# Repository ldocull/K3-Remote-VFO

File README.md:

# K3-Remote-VFO
Remote VFO and Button Interface for Elecraft, Kenwood and other radio transceivers

## Introduction
The system is comprised of two pieces
 - A Remote Controls Unit
 - A Connector Interface to the Rig 

The Connector Interface goes between the control PC and the Rig using classic RS-232. This system is not currently set up to support modern USB interfaces. The main Remote control is tethered to the Connector Interface using a RJ12 (6P/6J) straight-through cable.  Power (5VDC) is supplied to the device from a USB port or power supply to the Connector Interface via a micro-USB jack.

## About the Design Data

The Mechanics were designed in Fusion 360, A full step-assembly is in the repo which could be pulled into any modern CAD package for alteration.   

The construction is plastic. The case frame was FDM printed from PLA, and the top/bottom were laser cut from 
0.08" acrylic. The main-dial and keycaps were SLA (resin) printed on an [Elegoo Mars](https://www.elegoo.com/collections/3d-printing/products/elegoo-mars-3-lcd-3d-printer) printer.

The Electronics were designed in KiCAD. KiCAD is free and easy to use, so this should be a good start for further work. I used [JLCPCB](https://jlcpcb.com/) to manufacture the PCBs.

The Software is Arduino-based and runs on a [STM32F103C8 BlackPill](https://hobbycomponents.com/st-micro-electronics/960-stm32f103-black-pill-development-board). The project is in Visual Studio Code, and PlatformIO which are currently both free tools.  The Maple bootloader was installed to make the development quick and easy and is included in the repo.

## Updating Encoder and Key Definitions

The keys are assigned text-macros which are stored in non-volatile memory on the Remote unit. The encoder-wheel is handled the same way. The wheel can be pressed and therefore the operation has been divided into four "speeds" (as is indicated by the LEDs below the wheel.)  In the case of the encoder, the macros are also divided into four sets up ***"up"*** and ***"down"*** movements and the text contents are transmitted on each pulse of the wheel.

The default baud rate is ***38400*** and the Remote can be updated in-situ using a terminal emulator such as [RealTerm](https://realterm.sourceforge.io/).   

The following text could be uploaded to the remote.  `'$$$'` is used to mark the beginning of the upload, and `'&&&'` is used to end the upload.  Note that the macros are defined as ```<Kx> text message </K>'``` and `<Ex> text message </E>`. 

> (*Note the messages defined below are for the Elecraft K3.)*

```
$$$			// 3 dollar start of file

<K0>SWT11;</K>  //  A/B  menus stuff here...
<K1>SWT13;</K>  // A->B
<K2>SWT42;</K>  // SPOT

<K3>SWT29;</K>  // XFILT

<K4>SWT21;</K>  // M1-M2
<K5>SWT31;</K>  
<K6>SWT35;</K>  
<K7>SWT39;</K>  

<E0>UP4;</E>    // encoder modes here 0-3, increment/decrement
<E1>DN4;</E>    

<E2>UP8;</E>    
<E3>DN8;</E>    

<E4>UP1;</E>    
<E5>DN1;</E>    

<E6>UP0;</E>    
<E7>DN0;</E>	// end of file is ampersand

&&&
```

### Enjoy, 73,  de WR9R

___
Let us know that this work has been helpful to you.  Any proceeds will be used to offset expenses and further the art.

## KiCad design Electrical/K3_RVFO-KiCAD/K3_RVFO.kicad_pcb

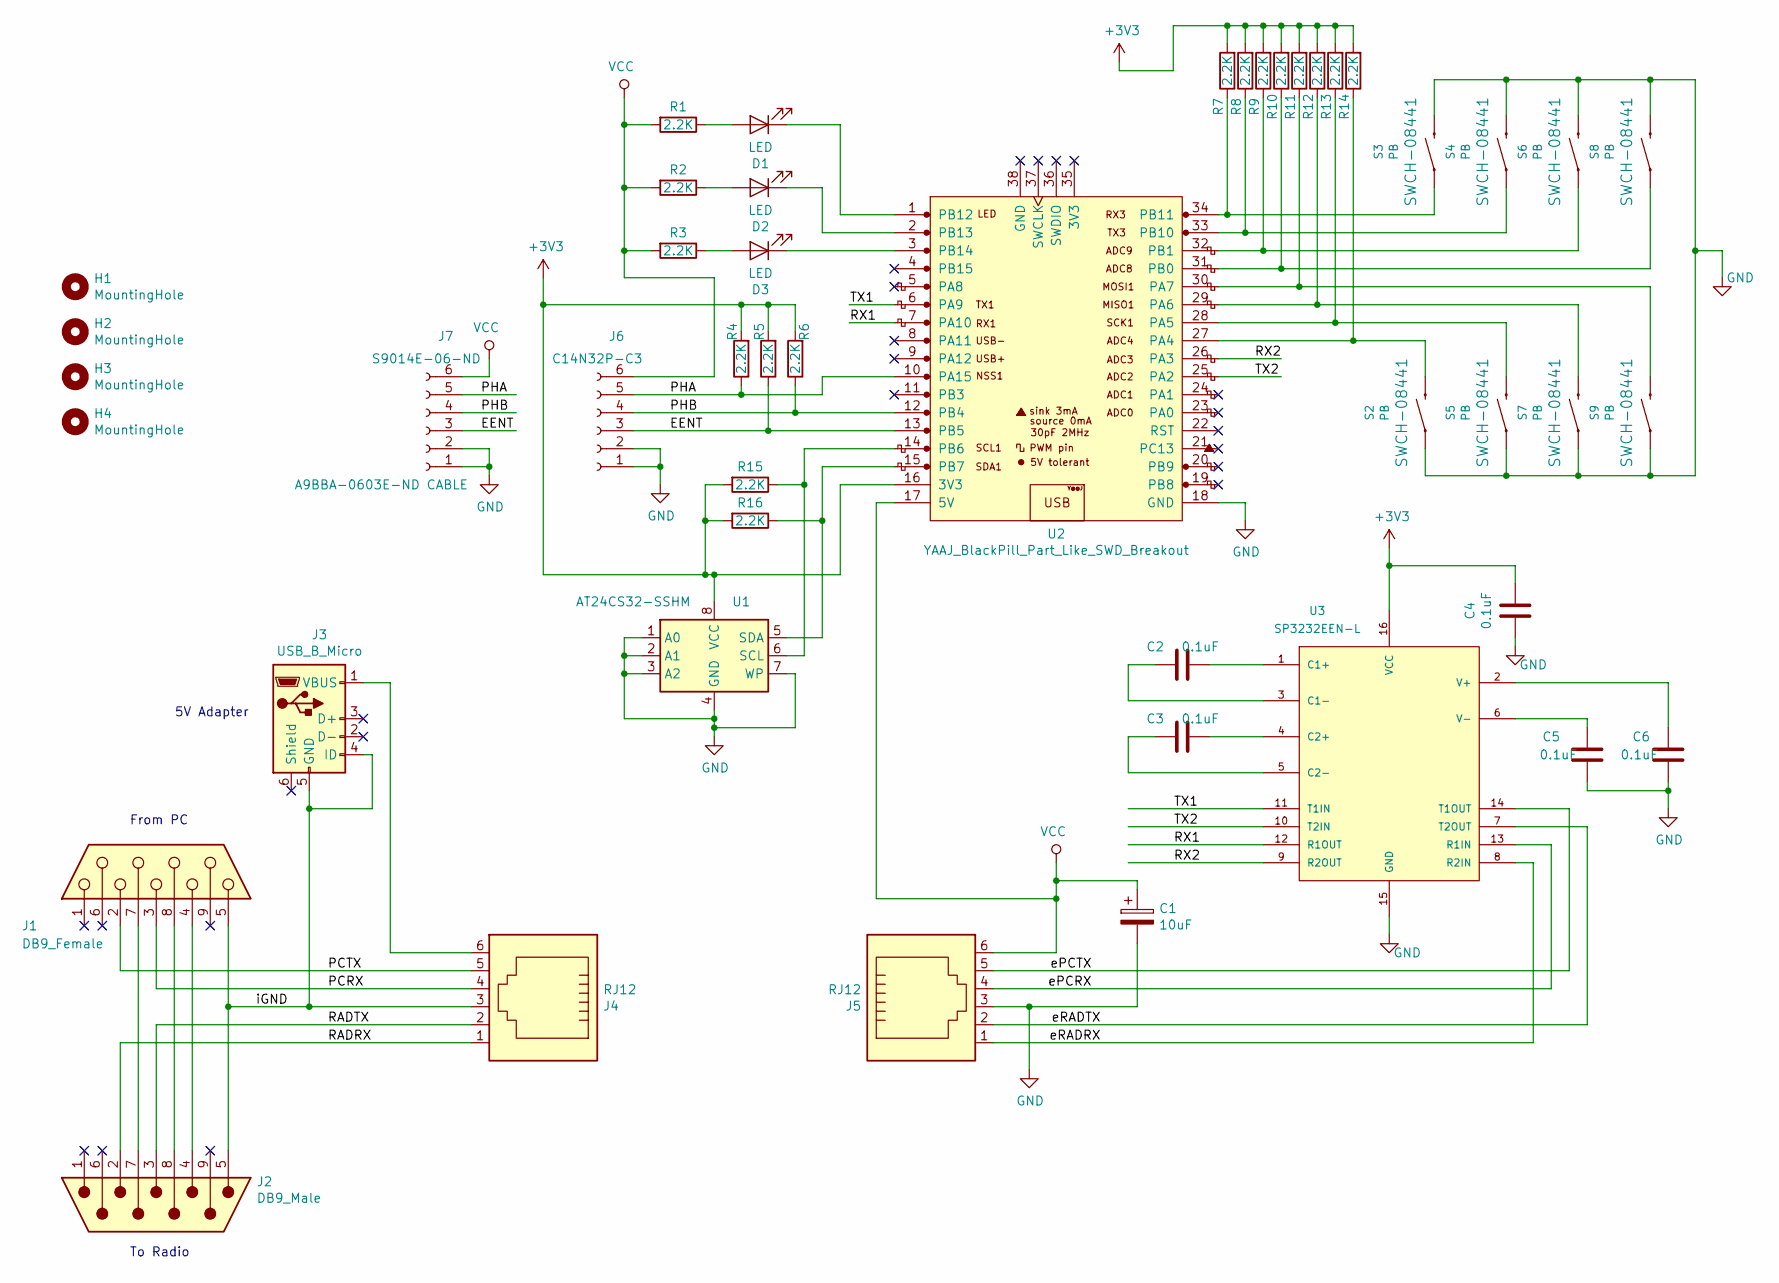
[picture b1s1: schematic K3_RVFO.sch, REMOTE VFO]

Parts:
C1: 10uF; CP_Elec_4x5.7; JLCPCB C59932
C2, C3, C4, C5, C6: 0.1uF; 0805; JLCPCB C2594299
D1, D2, D3: LED; LED_3MM
H1, H2, H3, H4: MountingHole; MountingHole_3mm_Pad
J1: DB9_Female; DSUB-9_Female_Horizontal_P2.77x2.84mm_EdgePinOffset4.94mm_H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
J2: DB9_Male; DSUB-9_Male_Horizontal_P2.77x2.84mm_EdgePinOffset4.94mm_Hou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
J3: USB_B_Micro; USB_Micro-B_Molex-105017-0001; JLCPCB C10418
J4, J5: RJ12; RJ12_Amphenol_54601
J6: C14N32P-C3; PinHeader_1x06_P2.54mm_Vertical
J7: S9014E-06-ND; PinHeader_1x06_P1.27mm_Vertical
R1, R2, R3, R4, R5, R6, R7, R8, R9, R10, R11, R12, R13, R14, R15, R16: 2.2K; R_0805_2012Metric; JLCPCB C17520
S2, S3, S4, S5, S6, S7, S8, S9: PB; TACTILE_SWITCH_PTH_6.0MM
U1: AT24CS32-SSHM; SOIC-8_3.9x4.9mm_P1.27mm
U2: YAAJ_BlackPill_Part_Like_SWD_Breakout; YAAJ_BlackPill_SWD_2
U3: SP3232EEN-L; SO16; JLCPCB C9378

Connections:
+3V3: C4.1, R4.2, R5.2, R6.2, R7.2, R8.2, R9.2, R10.2, R11.2, R12.2, R13.2, R14.2, R15.2, R16.2, U1.8 (VCC), U2.16 (3V3), U3.16 (VCC)
/EENT: J6.3, J7.3, R5.1, U2.13 (PB5)
/PCRX: J1.3, J4.4
/PCTX: J1.2, J4.5
/PHA: J6.5, J7.5, R4.1, U2.10 (PA15)
/PHB: J6.4, J7.4, R6.1, U2.12 (PB4)
/RADRX: J2.2, J4.1
/RADTX: J2.3, J4.2
/RX1: U2.7 (PA10), U3.12 (R1OUT)
/RX2: U2.26 (PA3), U3.9 (R2OUT)
/TX1: U2.6 (PA9), U3.11 (T1IN)
/TX2: U2.25 (PA2), U3.10 (T2IN)
/ePCRX: J5.4, U3.13 (R1IN)
/ePCTX: J5.5, U3.14 (T1OUT)
/eRADRX: J5.1, U3.8 (R2IN)
/eRADTX: J5.2, U3.7 (T2OUT)
/iGND: J1.5, J2.5, J3.4 (ID), J3.5 (GND), J4.3
GND: C1.2, C4.2, C5.2, C6.2, J5.3, J6.1, J6.2, J7.1, J7.2, S2.1, S3.3 (2), S4.3 (2), S5.1, S6.3 (2), S7.1, S8.3 (2), S9.1, U1.1 (A0), U1.2 (A1), U1.3 (A2), U1.4 (GND), U1.7 (WP), U2.18 (GND), U3.15 (GND)
unnamed: C2.1, U3.1 (C1+)
unnamed: C2.2, U3.3 (C1-)
unnamed: C3.1, U3.4 (C2+)
unnamed: C3.2, U3.5 (C2-)
unnamed: C5.1, U3.6 (V-)
unnamed: C6.1, U3.2 (V+)
unnamed: D1.1 (K), U2.1 (PB12)
unnamed: D1.2 (A), R1.1
unnamed: D2.1 (K), U2.2 (PB13)
unnamed: D2.2 (A), R2.1
unnamed: D3.1 (K), U2.3 (PB14)
unnamed: D3.2 (A), R3.1
unnamed: J1.4, J2.4
unnamed: J1.7, J2.7
unnamed: J1.8, J2.8
unnamed: J3.1 (VBUS), J4.6
unnamed: R7.1, S3.1, U2.34 (PB11)
unnamed: R8.1, S4.1, U2.33 (PB10)
unnamed: R9.1, S6.1, U2.32 (PB1)
unnamed: R10.1, S8.1, U2.31 (PB0)
unnamed: R11.1, S9.3 (2), U2.30 (PA7)
unnamed: R12.1, S7.3 (2), U2.29 (PA6)
unnamed: R13.1, S5.3 (2), U2.28 (PA5)
unnamed: R14.1, S2.3 (2), U2.27 (PA4)
unnamed: R15.1, U1.6 (SCL), U2.14 (PB6)
unnamed: R16.1, U1.5 (SDA), U2.15 (PB7)
VCC: C1.1, J5.6, J6.6, J7.6, R1.2, R2.2, R3.2, U2.17 (5V)

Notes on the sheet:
5V Adapter
From PC
To Radio

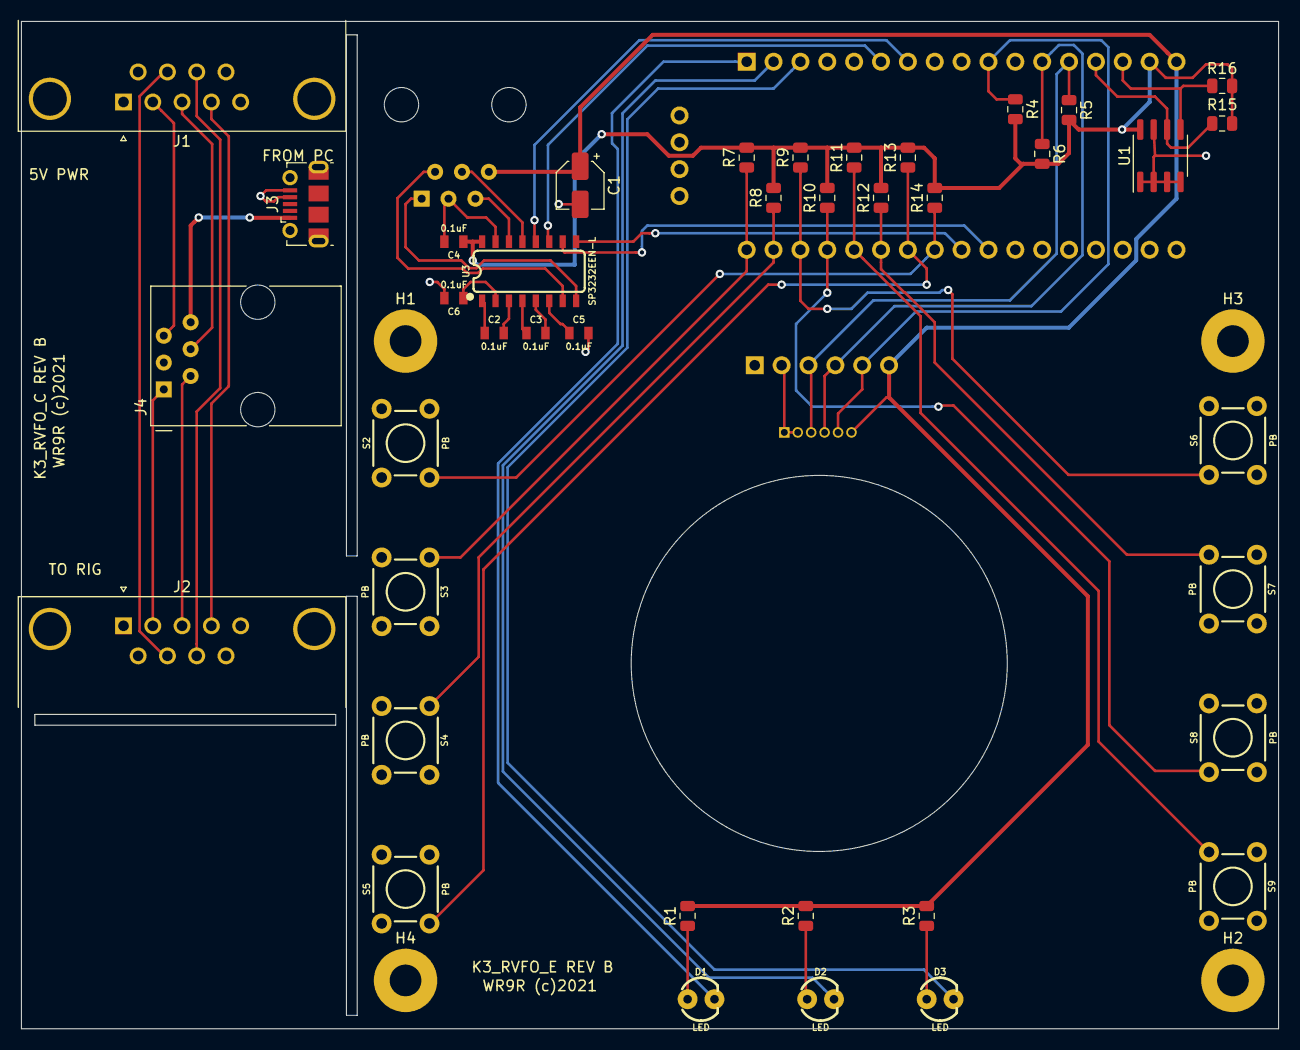
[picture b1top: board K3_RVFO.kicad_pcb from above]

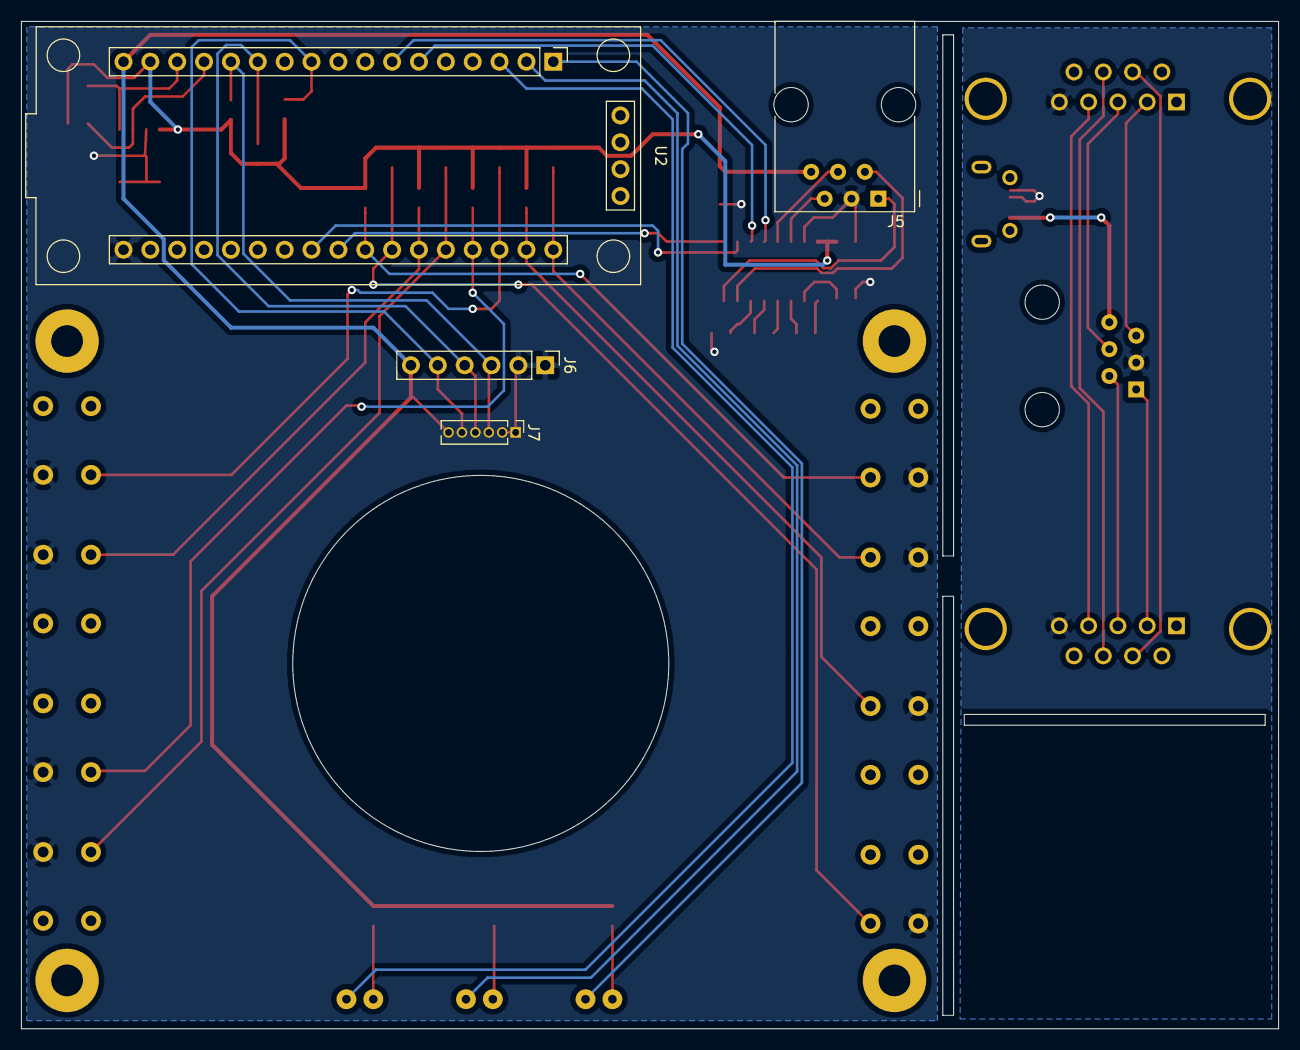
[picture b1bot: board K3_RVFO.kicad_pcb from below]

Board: 2 copper layers, 118.9 x 95.3 mm, 47 parts (4 on the bottom side), 45 nets.

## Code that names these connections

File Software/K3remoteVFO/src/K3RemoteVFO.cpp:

/*
  K3 REMOTE VFO

  2021/12/22
  (c)WR9R  Larry O'Cull 2021  LDO Systems LLC
 */

#include <Arduino.h>
#include "wheel.h"
#include "EE24C32.h"

EE24C32 EEPROM(0x50);
USBSerial COMM_PORT;

#define PC_LINK Serial1
#define RIG_LINK Serial2
#define HOST_SIDE PC_LINK
//#define HOST_SIDE COMM_PORT  // -- for using USB port for configuration

#define KEY0  PA4
#define KEY1  PB11
#define KEY2  PB10
#define KEY3  PA5
#define KEY4  PB1
#define KEY5  PA6
#define KEY6  PB0
#define KEY7  PA7
#define ENTER PB5

#define LED0  PB12
#define LED1  PB13
#define LED2  PB14

#define MAX_WHEEL_MODE 3
#define MAX_MESSAGE_INDEX 8
#define MAX_ENCMES_INDEX 8
#define MAX_MESSAGE_SIZE 128

struct EPROM_PLAN 
{
    uint8_t checkValue = 0x14;
    
    char keyMessage[MAX_MESSAGE_INDEX][MAX_MESSAGE_SIZE] = {
        {"SWT09;"},   // BAND +
        {"SWT10;"},   // BAMD -
        {"SWT17;"},   // MODE ++
        {"SWT29;"},   // XFIL
        {"SWT21;"},   // M1-M4...
        {"SWT31;"},
        {"SWT35;"},
        {"SWT39;"}};
    
    char encMessage[MAX_MESSAGE_INDEX][MAX_MESSAGE_SIZE] = {
        {"UP0;"},    // encoder base
        {"DN0;"},
        {"UP1;"},    // encoder up 1 level
        {"DN1;"},
        {"UP8;"},    // encoder up 2nd level
        {"DN8;"},
        {"UP4;"},    // encoder up 3nd level
        {"DN4;"}};

    int wheelMode = 0;

} rigSettings, backupSettings;

int initialized = 0;

// the setup function runs once when you press reset or power the board
void setup() {
  // initialize digital pin PB1 as an output.
  pinMode(LED0, OUTPUT);
  pinMode(LED1, OUTPUT);
  pinMode(LED2, OUTPUT);

  pinMode(KEY0,INPUT_PULLUP);
  pinMode(KEY1,INPUT_PULLUP);
  pinMode(KEY2,INPUT_PULLUP);
  pinMode(KEY3,INPUT_PULLUP);
  pinMode(KEY4,INPUT_PULLUP);
  pinMode(KEY5,INPUT_PULLUP);
  pinMode(KEY6,INPUT_PULLUP);
  pinMode(KEY7,INPUT_PULLUP);
  pinMode(ENTER,INPUT_PULLUP);

  PC_LINK.begin(38400); // PC side of life..  

  pinMode(PA3,INPUT_PULLUP);
  pinMode(PA2,OUTPUT);
  RIG_LINK.begin(38400); // Rig side of life..
  init_Encoder();
   COMM_PORT.begin(115200);
}

// lists the values of the stored message/macros for keys and encoder
void printMacros()
{
    int i;
      
    for(i=0; i< MAX_MESSAGE_INDEX; i++)
    {
      HOST_SIDE.print("<K");
      HOST_SIDE.print(i);
      HOST_SIDE.print(">");
      HOST_SIDE.print(rigSettings.keyMessage[i]);
      HOST_SIDE.println("</K>");
    }

    for(i=0; i< MAX_ENCMES_INDEX; i++)
    {
      HOST_SIDE.print("<E");
      HOST_SIDE.print(i);
      HOST_SIDE.print(">");
      HOST_SIDE.print(rigSettings.encMessage[i]);
      HOST_SIDE.println("</E>");
    }
}

// returns a key value 1-8 (9 for main dial), 0 if none pressed
int getKeyPress()
{
  if(!digitalRead(KEY0)) return 1;
  if(!digitalRead(KEY1)) return 2;
  if(!digitalRead(KEY2)) return 3;
  if(!digitalRead(KEY3)) return 4;
  if(!digitalRead(KEY4)) return 5;
  if(!digitalRead(KEY5)) return 6;
  if(!digitalRead(KEY6)) return 7;
  if(!digitalRead(KEY7)) return 8;
  if(!digitalRead(ENTER)) return 9;
  return 0;
}

// set LEDs based on lower 3-bits of 'n'
void setLEDs(int n)
{
  digitalWrite(LED0,HIGH);
  digitalWrite(LED1,HIGH);
  digitalWrite(LED2,HIGH);

  if(n & 1)
      digitalWrite(LED0,LOW);
  if(n & 2)
      digitalWrite(LED1,LOW);
  if(n & 4)
      digitalWrite(LED2,LOW);
}

void saveRigSettings(int force)
{
    uint8_t *rp, *bp;

    rp = (uint8_t *)&rigSettings;
    bp = (uint8_t *)&backupSettings;       // save any changed memories to EEPROM
    for (int i=0; i < (int) sizeof(rigSettings); i++)
    {
        if((*rp != *bp) || (force != 0))
        {
            EEPROM.write(i, *rp);
            *bp = *rp;
            // chk = 1;
        }    
        bp++;
        rp++;
    }
}

void restoreRigSettings(void)
{
    uint8_t *rp,*bp;

    if(rigSettings.checkValue != EEPROM.read(0))
    {
        saveRigSettings(1); // factory defaults on 1st time on.
    } 
    else
    {
        rp = (uint8_t *)&rigSettings;      // copy EEPROM to rig and backup (comparison) local memory
        bp = (uint8_t *)&backupSettings;
        for (int i=0; i < (int) sizeof(rigSettings); i++)
        {
            *rp = *bp = EEPROM.read(i);
            rp++;
            bp++;
        }   
    }     
}

// blocking read character routine..
char getchBlocking()
{
  char c;
  while(!HOST_SIDE.available()) 
      ;
  c = HOST_SIDE.read();    
  HOST_SIDE.write( c );
  return c;
}  

int engSeqCnt = 0;  // escape sequence counter..

// this routing watches the stream from the PC 
// and if '$$$' is detected, then parses and stores macro definitions
// until '&' is detected.  When '&' arrives, the macros are saved
// to EEPROM and then listed back to the 'console'
void commandProc()
{
    char c, t, *p;
    int i;

    if(!HOST_SIDE.available()) return;
    
    c = HOST_SIDE.peek();
    if(c == '$')
    {
      c = getchBlocking();
      engSeqCnt++;
    }
    else
      engSeqCnt = 0;

    if(engSeqCnt >= 3)
    {
      HOST_SIDE.print('>'); // prompt to indicate terminal mode..
      c = getchBlocking();
      while(1)
      {
        if( c == '?')
        {
          printMacros(); 
        }

        if( c == '&') 
        {
          saveRigSettings(0);
          printMacros();   
          return;
        }

        if( c == '<')
        {
          t = getchBlocking();  // grab K or E
          c = getchBlocking();  // and the index
          i = (int) c - '0';
          getchBlocking();      // eat the carrot..

          HOST_SIDE.print(t);
          HOST_SIDE.print(i);
          HOST_SIDE.println(":");

          if(i < MAX_MESSAGE_INDEX)
          {
            p = &rigSettings.keyMessage[i][0];
            if( t == 'E')
              p = &rigSettings.encMessage[i][0];

            while(1)
            { 
              c = getchBlocking();
              if( c == '<') break;
              *p++ = c;
            }
            *p = 0;  // terminate string...
          }
          getchBlocking();      // eat the slash..
          getchBlocking();      // eat the end mark..
          getchBlocking();      // eat the carrot..
        }
        c =  getchBlocking();   // next char...
      }
    } 
}

// the loop function runs over and over again forever
void loop() 
{
  char c;

  if(!initialized)
  {
    delay(8000);
    COMM_PORT.println("Initialize VFO..");
    // printMacros();    
    delay(1000);
    initialized = 1;
    setLEDs(0);
    COMM_PORT.println("Initialize I2C..");
      
    EEPROM.begin(&Wire);
    int test = EEPROM.read(0x0);
    COMM_PORT.print("EEPROM TEST: ");
    COMM_PORT.println(test, HEX);
    restoreRigSettings();     // get rig state from EEPROM
    
    setLEDs(1<<rigSettings.wheelMode); // restore LEDs to reflect last state
  }

  if(initialized)
  {
    commandProc();

    while(PC_LINK.available() || RIG_LINK.available())
    {
      while(PC_LINK.available())  // exchange left<->right
      { 
        c = PC_LINK.read();
        RIG_LINK.write(c);
      }
      while(RIG_LINK.available())
      {
        c = RIG_LINK.read();
        PC_LINK.write(c);
      }
      delay(20);  // look for opening in communications
    }

    if(getKeyPress() != 0) // look for key presses..
    {
      delay(20);
      if(getKeyPress() != 0)  // debounce on (pressed)
      {
        if(getKeyPress() < 9)     // macro key preses
        {  
          RIG_LINK.print(rigSettings.keyMessage[getKeyPress()-1]);
        }
        else
        {
          rigSettings.wheelMode++;
          if(rigSettings.wheelMode > MAX_WHEEL_MODE)
            rigSettings.wheelMode = 0;
          setLEDs(1<<rigSettings.wheelMode);  // jog-wheel presses
          saveRigSettings(0);                 // save state to EEPROM
        }

        while(getKeyPress() != 0) // debounce off (released)
        delay(20);
      }
    }

    extern int wheelValue, lastWheelValue;

    processWheel();
    if(wheelValue != lastWheelValue)      // send macro message for appropriate mode, for up and down
    {
        if(lastWheelValue > wheelValue)
            RIG_LINK.print(rigSettings.encMessage[rigSettings.wheelMode*2]);
        else
            RIG_LINK.print(rigSettings.encMessage[(rigSettings.wheelMode*2)+1]);

        lastWheelValue = wheelValue;
    }
  }
}

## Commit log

2022-01-01 Initial commit 1/1/2022 - WR9R
2022-01-01 Added images..
2022-01-01 Added gerbers...
2022-01-01 Added PDF Schematic
2022-01-05 Adjusted slot width per G6CMV feedback
2022-01-05 Added zip of the gerbers for ease
2022-01-05 Added zip file of gerbers for ease as well as freeCAD project reference. Updated drill files.

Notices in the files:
Electrical/K3_RVFO-KiCAD/K3_RVFO.kicad_pcb:
WR9R (c)2021
